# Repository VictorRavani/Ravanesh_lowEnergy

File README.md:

# Ravanesh_lowEnergy
Repositório para armazenar os arquivos do projeto Ravanesh Low Energy, este projeto de hardware tem como objetivo o baixo consumo de energia quando o ESP32 entra em modo deep sleep, essa placa deve ser utilizada junto a um conversor USB SERIAL (ex.: CP2102).

# Imagem 3D da placa Ravanesh Low Energy

# Fabricação da Placa

# Montagem da placa

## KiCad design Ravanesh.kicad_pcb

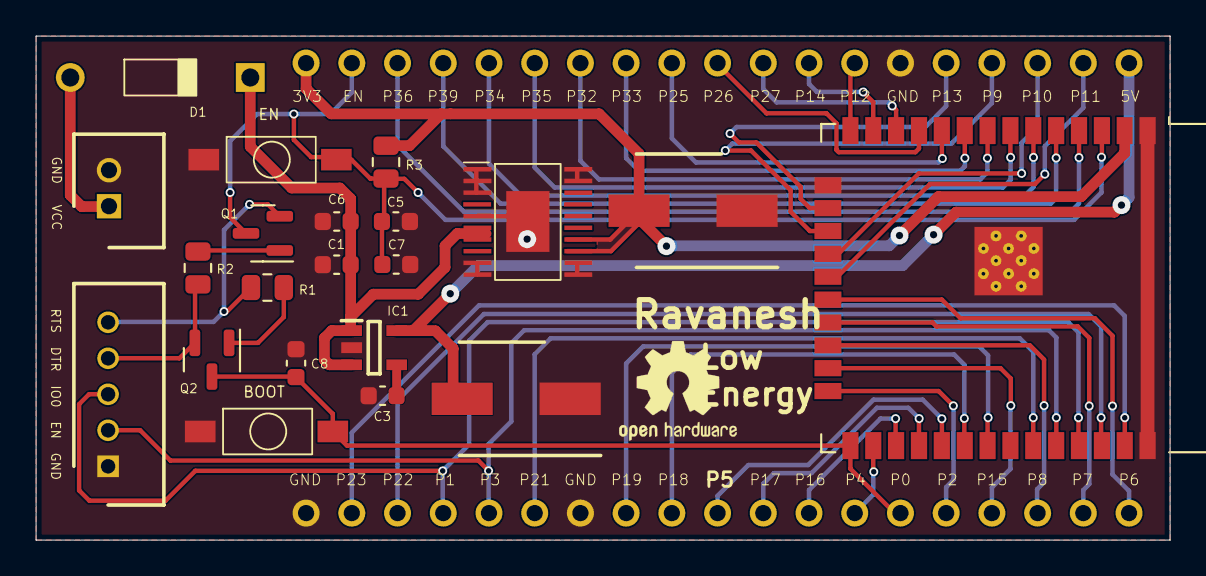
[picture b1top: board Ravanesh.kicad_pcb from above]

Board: 2 copper layers, 63.0 x 28.0 mm, 23 parts (0 on the bottom side), 43 nets.

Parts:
C1, C5, C6, C7, C8: 100nF; C_0603_1608Metric
C2, C4: 10uF; CAPAE630X610N
C3: 10nF; C_0603_1608Metric
D1: SB140-E3/54; Diodo
IC1: SPX3819M5-L-5-0_TR
J1: Header_Shrouded_2vias
J2, J3: Conn_01x19_Socket; Pin_header_19vias_Corrigido
J5: 440054-5; Header_Shrouded_5vias
Q1, Q2: BC817; SOT-23
R1, R2: 4K7; R_0805_2012Metric
R3: 10K; R_0805_2012Metric
SW1, SW2: SW_DPST_x2; SW_SPST_CK_KXT3_editado
U1: TPS76733QPWPG4; SOIC-0,65-20 vias
U2: ESP32-WROOM-32D

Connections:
+3V3: C2.2, J2.1, R3.1, U1.13, U1.14, U2.2 (VDD)
+5V: C4.2, IC1.5 (VOUT), J2.19
BAT: C1.1, C6.2, D1.2, IC1.1 (VIN), IC1.3 (EN), U1.6, U1.7
DTR: J5.4, Q2.2 (E), R2.1
EN: C5.1, C7.1, J2.2, Q1.3 (C), R3.2, SW2.2 (B), U2.3 (EN)
GND: C1.2, C2.1, C3.2, C4.1, C5.2, C6.1, C7.2, C8.2, IC1.2 (GND), J1.2, J2.14, J3.1, J3.7, J5.1, SW1.1 (A), SW2.1 (A), U1.1, U1.2, U1.3, U1.5, U1.9, U1.10, U1.11, U1.12, U1.19, U1.20, U1.21, U2.1 (GND), U2.15 (GND), U2.38 (GND), U2.39 (GND)
GPIO0: C8.1, J3.14, Q2.3 (C), SW1.2 (B), U2.25 (IO0)
GPIO1: J3.4, J5.3, U2.35 (TXD0/IO1)
GPIO2: J3.15, U2.24 (IO2)
GPIO3: J3.5, J5.2, U2.34 (RXD0/IO3)
GPIO4: J3.13, U2.26 (IO4)
GPIO5: J3.10, U2.29 (IO5)
GPIO6: J3.19, U2.20 (SCK/CLK)
GPIO7: J3.18, U2.21 (SDO/SD0)
GPIO8: J3.17, U2.22 (SDI/SD1)
GPIO9: J2.16, U2.17 (SHD/SD2)
GPIO10: J2.17, U2.18 (SWP/SD3)
GPIO11: J2.18, U2.19 (SCS/CMD)
GPIO12: J2.13, U2.14 (IO12)
GPIO13: J2.15, U2.16 (IO13)
GPIO14: J2.12, U2.13 (IO14)
GPIO15: J3.16, U2.23 (IO15)
GPIO16: J3.12, U2.27 (IO16)
GPIO17: J3.11, U2.28 (IO17)
GPIO18: J3.9, U2.30 (IO18)
GPIO19: J3.8, U2.31 (IO19)
GPIO21: J3.6, U2.33 (IO21)
GPIO22: J3.3, U2.36 (IO22)
GPIO23: J3.2, U2.37 (IO23)
GPIO25: J2.9, U2.10 (IO25)
GPIO26: J2.10, U2.11 (IO26)
GPIO27: J2.11, U2.12 (IO27)
GPIO32: J2.7, U2.8 (IO32)
GPIO33: J2.8, U2.9 (IO33)
GPIO34: J2.5, U2.6 (IO34)
GPIO35: J2.6, U2.7 (IO35)
GPIO36: J2.3, U2.4 (SENSOR_VP)
GPIO39: J2.4, U2.5 (SENSOR_VN)
unnamed: D1.1, J1.1
unnamed: C3.1, IC1.4 (ADJ/BYP)
unnamed: Q1.1 (B), R2.2
unnamed: Q2.1 (B), R1.2
RTS: J5.5, Q1.2 (E), R1.1

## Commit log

2023-05-11 primeiro commit utilizando o git bash
2023-05-11 teste do arquivo de texto
2023-05-11 teste do arquivo de texto2
2023-05-11 Add pdf com dias de layout de placa
2024-06-21 Create LICENSE
